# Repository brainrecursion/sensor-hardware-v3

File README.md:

# sensor-hardware-v3

Eagle schematic and pcb files for wireless temperature and humidity sensor.
See www.brainrecursion.com for more details.

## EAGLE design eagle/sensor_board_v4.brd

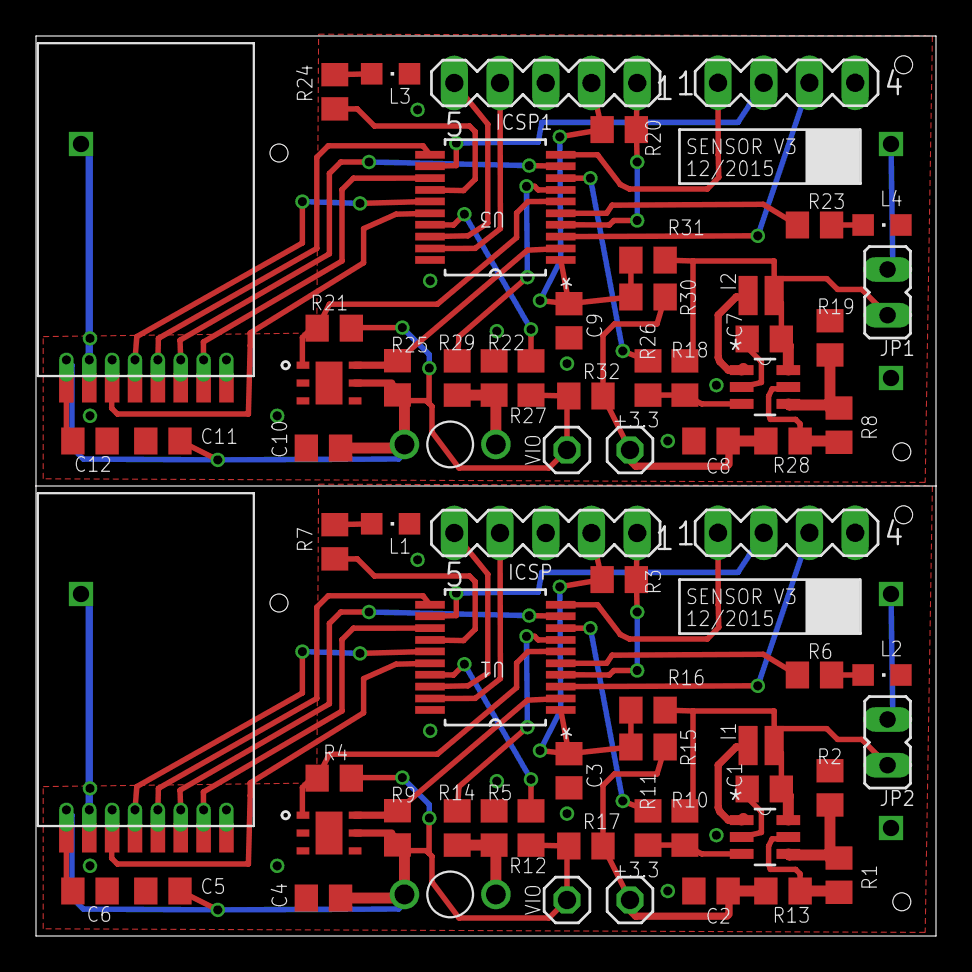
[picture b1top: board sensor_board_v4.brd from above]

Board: 2 copper layers, 50.0 x 50.0 mm, 72 parts (0 on the bottom side), 62 nets.

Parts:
C1, C2, C5, C7, C8, C11: 10uF; C0805
C3, C4, C6, C9, C10, C12: 100nF; C0805
I1, I2: EPL2014
ICSP, ICSP1: MA05-1
JP1, JP2: JP1
JP3, JP4, JP5, JP6: 1X01
L1, L3: RED; CHIPLED_0805
L2, L4: GREEN; CHIPLED_0805
LDR1, LDR2: LDR
M1, M2: WIRELESS-NRF24L01SMD; NRF24L01-SMD
R1, R8, R10, R18: 976k; R0805
R2, R19: 562k; R0805
R3, R4, R9, R14, R20, R21, R25, R29: 10k; R0805
R5, R22: 50k; R0805
R6, R7, R23, R24: 50R; R0805
R11, R12, R13, R15, R16, R17, R26, R27, R28, R30, R31, R32: 0R; R0805
SV1, SV2: MA04-1
U1, U3: PIC16LF1509-I/SS; SOP65P780X200-20N
U2, U4: SHT21; DFN300X300X110-7N
U$1, U$4: MCP1640CT-I/CHY; SOT95P270X145-6N
U$2, U$3: BATTAAA; BATT

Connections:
+3V1: C8.1, JP6.1, R28.1, R30.1, R32.2
+3V3: C2.1, JP5.1, R13.1, R15.1, R17.2
ALTPWR: R12.2, U1.17
ALTPWR1: R27.2, U3.17
GND: C1.2, C2.2, C3.2, C4.1, C5.1, C6.1, ICSP.3, L1.C, L2.C, M1.GND, M1.GND1, R2.1, R5.1, SV2.4, U1.20, U2.2, U$2.GND, U$2.GND1, U$4.2
GND1: C7.2, C8.2, C9.2, C10.1, C11.1, C12.1, ICSP1.3, L3.C, L4.C, M2.GND, M2.GND1, R19.1, R22.1, SV1.4, U3.20, U4.2, U$1.2, U$3.GND, U$3.GND1
LDR_DATA: R14.2, U1.7
LDR_DATA1: R29.2, U3.7
LED_G: R6.1, U1.5
LED_G1: R23.1, U3.5
LED_R: R7.1, U1.14
LED_R1: R24.1, U3.14
unnamed: I1.2, U$4.1
unnamed: R1.1, R2.2, U$4.4
unnamed: JP2.1, U$2.VDD
unnamed: R10.1, R11.1, U$4.3
unnamed: ICSP.4, U1.19
unnamed: L2.A, R6.2
unnamed: L1.A, R7.2
unnamed: ICSP.5, U1.18
unnamed: ICSP.1, R3.1, U1.4
unnamed: C3.1, ICSP.2, R3.2, R15.2, R16.2, U1.1
unnamed: LDR1.2, R5.2, R14.1
unnamed: R8.1, R19.2, U$1.4
unnamed: R1.2, R13.2, U$4.5
unnamed: L4.A, R23.2
unnamed: L3.A, R24.2
unnamed: ICSP1.4, U3.19
unnamed: ICSP1.5, U3.18
unnamed: ICSP1.1, R20.1, U3.4
unnamed: I2.2, U$1.1
unnamed: JP1.1, U$3.VDD
unnamed: R8.2, R28.2, U$1.5
unnamed: C9.1, ICSP1.2, R20.2, R30.2, R31.2, U3.1
unnamed: LDR2.2, R22.2, R29.1
unnamed: R18.1, R26.1, U$1.3
PWR_EN: R11.2, U1.8
PWR_EN1: R26.2, U3.8
RF_CE: M1.CE, M1.CE1, U1.16
RF_CE1: M2.CE, M2.CE1, U3.16
RF_CSN: M1.CSN, M1.CSN1, U1.15
RF_CSN1: M2.CSN, M2.CSN1, U3.15
RF_MISO: M1.MISO, M1.MISO1, U1.13
RF_MISO1: M2.MISO, M2.MISO1, U3.13
RF_MOSI: M1.MOSI, M1.MOSI1, U1.9
RF_MOSI1: M2.MOSI, M2.MOSI1, U3.9
RF_SCK: M1.SCK, M1.SCK1, U1.11
RF_SCK1: M2.SCK, M2.SCK1, U3.11
RX: SV2.2, U1.12
RX1: SV1.2, U3.12
SHT_SCL: R9.1, U1.2, U2.6
SHT_SCL1: R25.1, U3.2, U4.6
SHT_SDA: R4.2, U1.6, U2.1
SHT_SDA1: R21.2, U3.6, U4.1
SPARE: SV2.3, U1.3
SPARE1: SV1.3, U3.3
TX: SV2.1, U1.10
TX1: SV1.1, U3.10
VCCIO: C4.2, C5.2, C6.2, JP4.1, LDR1.1, M1.VCC, M1.VCC1, R4.1, R9.2, R12.1, R17.1, U2.5
VCCIO1: C10.2, C11.2, C12.2, JP3.1, LDR2.1, M2.VCC, M2.VCC1, R21.1, R25.2, R27.1, R32.1, U4.5
VDD: C1.1, I1.1, JP2.2, R10.2, R16.1, U$4.6
VDD1: C7.1, I2.1, JP1.2, R18.2, R31.1, U$1.6

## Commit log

2016-03-10 Working sensor board design

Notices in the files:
parts and their libraries:
diy-modules: Released under the Creative Commons Attribution 4.0 International License: http://creativecommons.org/licenses/by/4.0
